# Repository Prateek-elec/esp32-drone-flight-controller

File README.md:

# ESP32 Drone Control Board (KiCad)

Custom ESP32-based drone control PCB designed in KiCad.
This board is made for embedded drone/robotics applications with onboard power + sensor + control headers.

---

## 🔥 Key Features
- ESP32 microcontroller (WiFi/Bluetooth)
- USB-C power input
- LiPo charging circuit
- 3.3V power regulation
- IMU sensor interface (example: MPU6050)
- Motor/servo output headers
- Debug / programming interface
- Status LEDs

---

## 🧠 What I worked on
✅ Schematic design  
✅ PCB layout and routing  
✅ Power section design (USB + battery + regulation)  
✅ Sensor + interface planning  
✅ Connectivity + headers for expansion

---

## 📷 PCB Preview

## 📄 Schematic Preview

---

## 📂 Repository Structure
- `hardware/kicad/` → KiCad project files
- `docs/images/` → PCB + schematic images
- `fabrication/` → Gerbers/BOM (optional)
- `firmware/` → Flight firmware (future update)

---

## 🛠 Tools Used
- KiCad
- ESP32 ecosystem

---

## 🚀 Future Improvements
- Add barometer (BMP/BME)
- Add better power filtering
- Add ESC signal conditioning
- Add full ArduPilot / custom firmware integration

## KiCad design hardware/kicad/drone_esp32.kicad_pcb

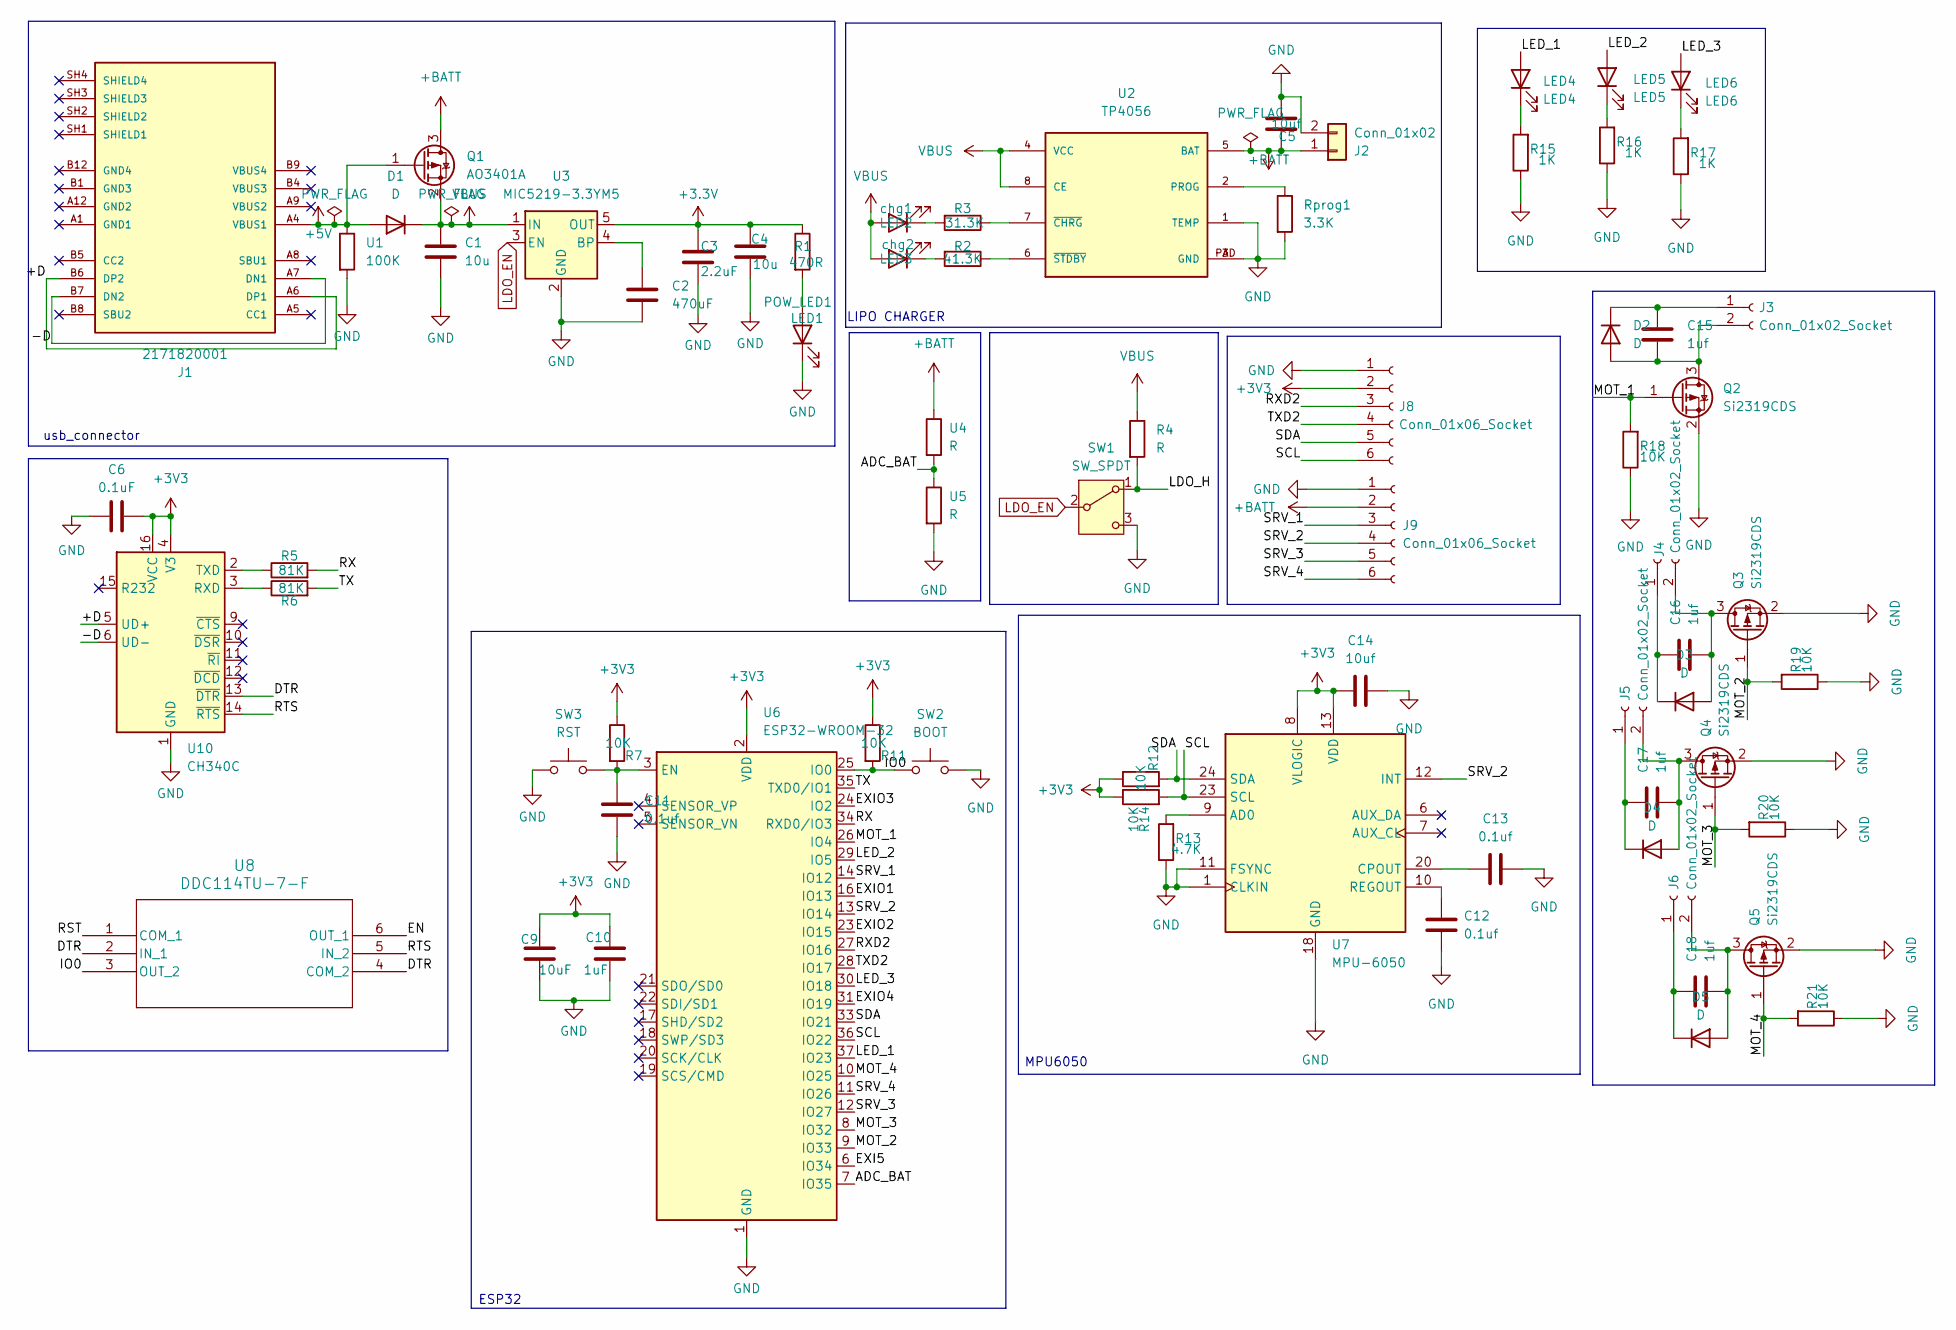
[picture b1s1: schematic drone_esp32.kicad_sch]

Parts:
C1, C4: 10u; C_0603_1608Metric
C2: 470uF; C_0603_1608Metric
C3: 2.2uF; C_0805_2012Metric
C5, C14: 10uf; C_0603_1608Metric
C6: 0.1uF; C_0603_1608Metric
C9: 10uF; C_0603_1608Metric
C10: 1uF; C_0603_1608Metric
C11, C12, C13: 0.1uf; C_0603_1608Metric
C15, C16, C17, C18: 1uf; C_0603_1608Metric
D1: D; D_SMA
D2, D3, D4, D5: D; D_SOD-123
J1: 2171820001; MOLEX_2171820001; PARTREV B
J2: Conn_01x02; JST_PH_B2B-PH-K_1x02_P2.00mm_Vertical
J3, J4, J5, J6: Conn_01x02_Socket; JST_PH_B2B-PH-K_1x02_P2.00mm_Vertical
J8, J9: Conn_01x06_Socket; PinHeader_1x06_P1.00mm_Vertical
LED4: LED4; LED_0201_0603Metric
LED5: LED5; LED_0201_0603Metric
LED6: LED6; LED_0201_0603Metric
POW_LED1: LED1; LED_0201_0603Metric
Q1: AO3401A; SOT-23
Q2, Q3, Q4, Q5: Si2319CDS; SOT-23
R1: 470R; R_0603_1608Metric
R2: 41.3K; R_0603_1608Metric
R3: 31.3K; R_0603_1608Metric
R4: R; R_0603_1608Metric
R5, R6: 81K; R_0603_1608Metric
R7, R11, R12, R14, R18, R19, R20, R21: 10K; R_0603_1608Metric
R13: 4.7K; R_0603_1608Metric
R15, R16, R17: 1K; R_0603_1608Metric
Rprog1: 3.3K; D_SOD-123
SW1: SW_SPDT; SW_SPDT_PCM12
SW2: BOOT; SW_Push_1P1T-MP_NO_Horizontal_Alps_SKRTLAE010
SW3: RST; SW_Push_1P1T-MP_NO_Horizontal_Alps_SKRTLAE010
U1: 100K; R_0201_0603Metric
U2: TP4056; SOIC-8_3.9x4.9mm_P1.27mm
U3: MIC5219-3.3YM5; SOT-23-5
U4, U5: R; R_0201_0603Metric
U6: ESP32-WROOM-32
U7: MPU-6050; InvenSense_QFN-24_4x4mm_P0.5mm
U8: DDC114TU-7-F; SOT_363_DIO
U10: CH340C; SOIC-16_3.9x9.9mm_P1.27mm
chg1: LED2; LED_0201_0603Metric
chg2: LED3; LED_0201_0603Metric

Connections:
+3.3V: C3.1, C4.1, R1.1, U3.5 (OUT)
+3V3: C6.2, C9.2, C10.2, C14.1, J8.2, R7.1, R11.1, R12.1, R14.1, U6.2 (VDD), U7.8 (VLOGIC), U7.13 (VDD), U10.4 (V3), U10.16 (VCC)
+5V: D1.2 (A), J1.A4 (VBUS1), Q1.1 (G), U1.1
+BATT: C5.2, J2.1, J9.2, Q1.3 (D), U2.5 (BAT), U4.1
/+D: J1.A6 (DP1), J1.B6 (DP2), U10.5 (UD+)
/-D: J1.A7 (DN1), J1.B7 (DN2), U10.6 (UD-)
/ADC_BAT: U4.2, U5.1, U6.7 (IO35)
/DTR: U8.2 (IN_1), U8.4 (COM_2), U10.13 (~DTR)
/EN: U8.6 (OUT_1)
/EXI5: U6.6 (IO34)
/EXIO1: U6.16 (IO13)
/EXIO2: U6.23 (IO15)
/EXIO3: U6.24 (IO2)
/EXIO4: U6.31 (IO19)
/IO0: R11.2, SW2.1, U6.25 (IO0), U8.3 (OUT_2)
/LDO_H: R4.2, SW1.1 (A)
/LED_1: LED4.2 (A), U6.37 (IO23)
/LED_2: LED5.2 (A), U6.29 (IO5)
/LED_3: LED6.2 (A), U6.30 (IO18)
/MOT_1: Q2.1 (G), R18.2, U6.26 (IO4)
/MOT_2: Q3.1 (G), R19.2, U6.9 (IO33)
/MOT_3: Q4.1 (G), R20.2, U6.8 (IO32)
/MOT_4: Q5.1 (G), R21.2, U6.10 (IO25)
/RST: U8.1 (COM_1)
/RTS: U8.5 (IN_2), U10.14 (~RTS)
/RX: R5.2, U6.34 (RXD0/IO3)
/RXD2: J8.3, U6.27 (IO16)
/SCL: J8.6, R14.2, U6.36 (IO22), U7.23 (SCL)
/SDA: J8.5, R12.2, U6.33 (IO21), U7.24 (SDA)
/SRV_1: J9.3, U6.14 (IO12)
/SRV_2: J9.4, U6.13 (IO14), U7.12 (INT)
/SRV_3: J9.5, U6.12 (IO27)
/SRV_4: J9.6, U6.11 (IO26)
/TX: R6.2, U6.35 (TXD0/IO1)
/TXD2: J8.4, U6.28 (IO17)
GND: C1.2, C2.2, C3.2, C4.2, C5.1, C6.1, C9.1, C10.1, C11.2, C12.1, C13.2, C14.2, J2.2, J8.1, J9.1, POW_LED1.1 (K), Q2.2 (S), Q3.2 (S), Q4.2 (S), Q5.2 (S), R13.1, R15.1, R16.1, R17.1, R18.1, R19.1, R20.1, R21.1, Rprog1.2, SW1.3 (C), SW2.2, SW3.1, U1.2, U2.1 (TEMP), U2.3 (GND), U2.PAD (GND), U3.2 (GND), U5.2, U6.1 (GND), U6.15 (GND), U6.38 (GND), U6.39 (GND), U7.1 (CLKIN), U7.11 (FSYNC), U7.18 (GND), U10.1 (GND)
LDO_EN: SW1.2 (B), U3.3 (EN)
unnamed: C15.1, D2.2 (A), J3.2, Q2.3 (D)
unnamed: C15.2, D2.1 (K), J3.1
unnamed: C16.1, D3.2 (A), J4.2, Q3.3 (D)
unnamed: C16.2, D3.1 (K), J4.1
unnamed: C17.1, D4.2 (A), J5.2, Q4.3 (D)
unnamed: C17.2, D4.1 (K), J5.1
unnamed: C18.1, D5.2 (A), J6.2, Q5.3 (D)
unnamed: C18.2, D5.1 (K), J6.1
unnamed: LED4.1 (K), R15.2
unnamed: LED5.1 (K), R16.2
unnamed: LED6.1 (K), R17.2
unnamed: POW_LED1.2 (A), R1.2
unnamed: Rprog1.1, U2.2 (PROG)
unnamed: R3.1, U2.7 (~CHRG)
unnamed: R2.1, U2.6 (~STDBY)
unnamed: C2.1, U3.4 (BP)
unnamed: C11.1, R7.2, SW3.2, U6.3 (EN)
unnamed: R13.2, U7.9 (AD0)
unnamed: C13.1, U7.20 (CPOUT)
unnamed: C12.2, U7.10 (REGOUT)
unnamed: R6.1, U10.3 (RXD)
unnamed: R5.1, U10.2 (TXD)
unnamed: R3.2, chg1.1 (K)
unnamed: R2.2, chg2.1 (K)
VBUS: C1.1, D1.1 (K), Q1.2 (S), R4.1, U2.4 (VCC), U2.8 (CE), U3.1 (IN), chg1.2 (A), chg2.2 (A)

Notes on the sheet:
ESP32
MPU6050
usb_connector
LIPO CHARGER

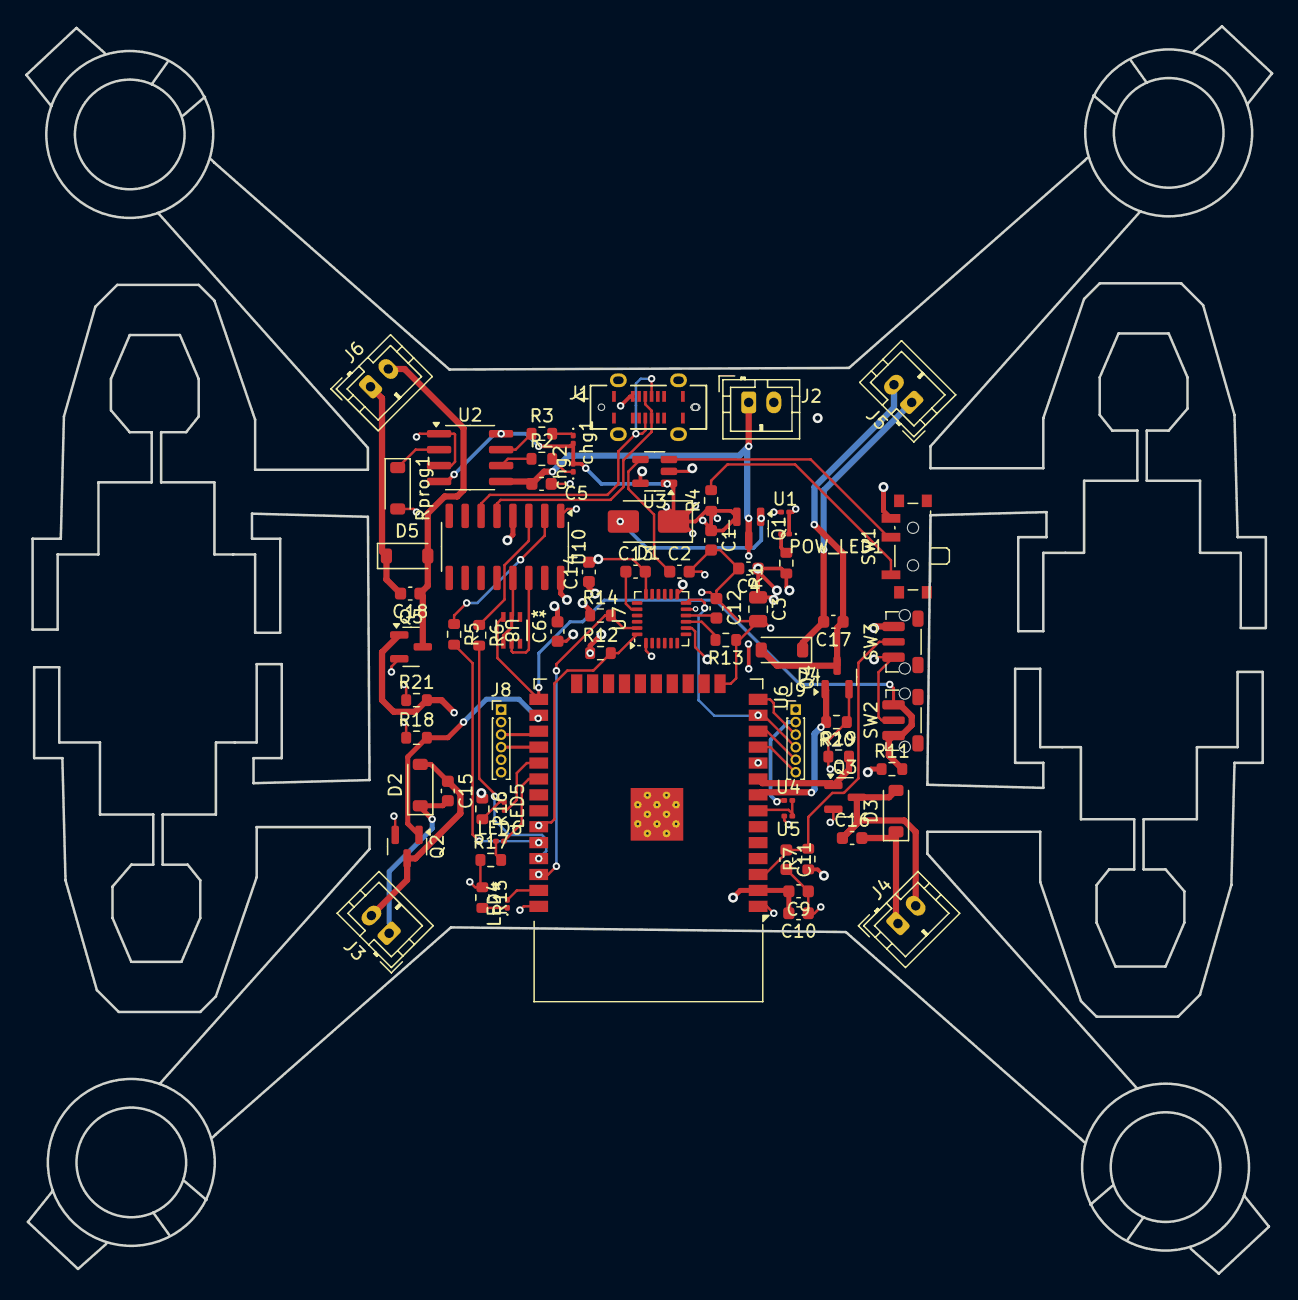
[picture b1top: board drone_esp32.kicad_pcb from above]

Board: 4 copper layers, 99.4 x 99.5 mm, 71 parts (0 on the bottom side), 55 nets.
